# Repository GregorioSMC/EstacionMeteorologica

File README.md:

# Estacion Meteorologica
Diseño en software Eagle 
<hr>
<ul>
	<li> PCB Conexión ESP8266 (NodeMCU) y display 16X2 mediante protocolo i2C </li>
	<li> Conexion Sensor DHT11 </li>
	<li> 4 pines GPIO para Activacion Pre-Actuadores  </li>
</ul>

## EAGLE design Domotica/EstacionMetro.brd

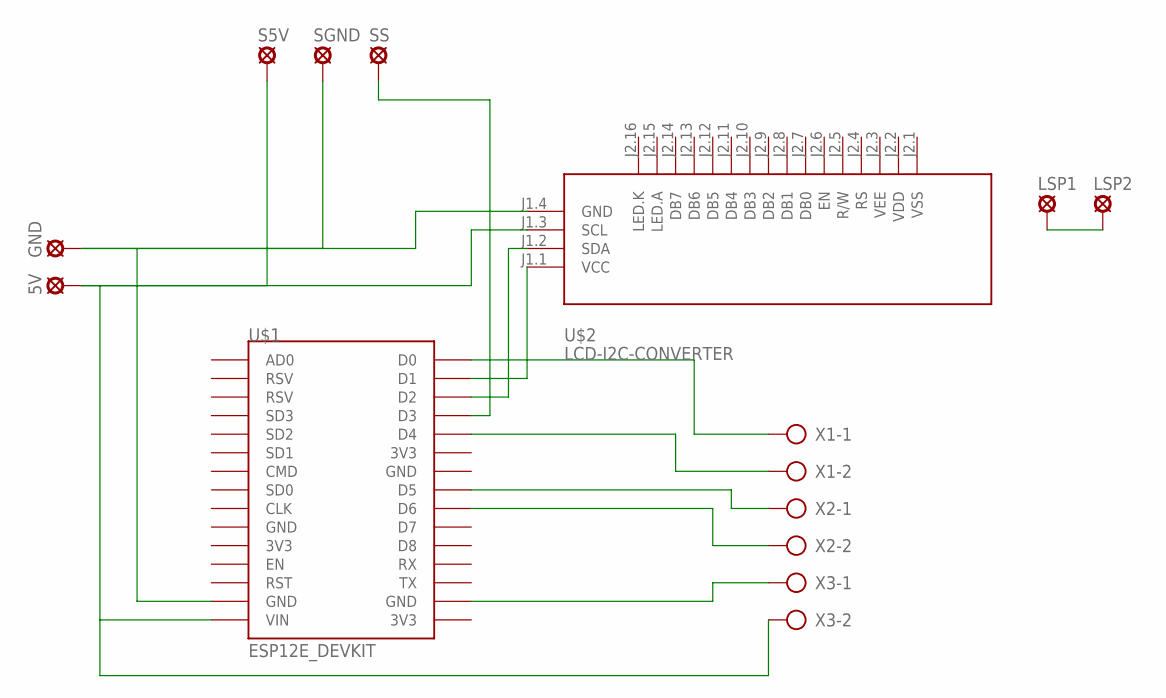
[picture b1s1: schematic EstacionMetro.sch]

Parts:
5V: SE11
GND: SE11
LSP1, LSP2: SE11
S5V: SE11
SGND: SE11
SS: SE11
U$1: ESP12E_DEVKIT
U$2: LCD-I2C-CONVERTER
X1, X2, X3: AK500/2

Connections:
unnamed: SS.MP, U$1.D3
unnamed: 5V.MP, S5V.MP, U$1.VIN, U$2.J1.3 (SCL), X3.2
unnamed: U$1.D1, U$2.J1.1 (VCC)
unnamed: U$1.D2, U$2.J1.2 (SDA)
unnamed: LSP1.MP, LSP2.MP
unnamed: GND.MP, SGND.MP, U$1.GND@1 (GND), U$2.J1.4 (GND)
unnamed: U$1.D0, X1.1
unnamed: U$1.D4, X1.2
unnamed: U$1.D5, X2.1
unnamed: U$1.D6, X2.2
unnamed: U$1.GND@3 (GND), X3.1

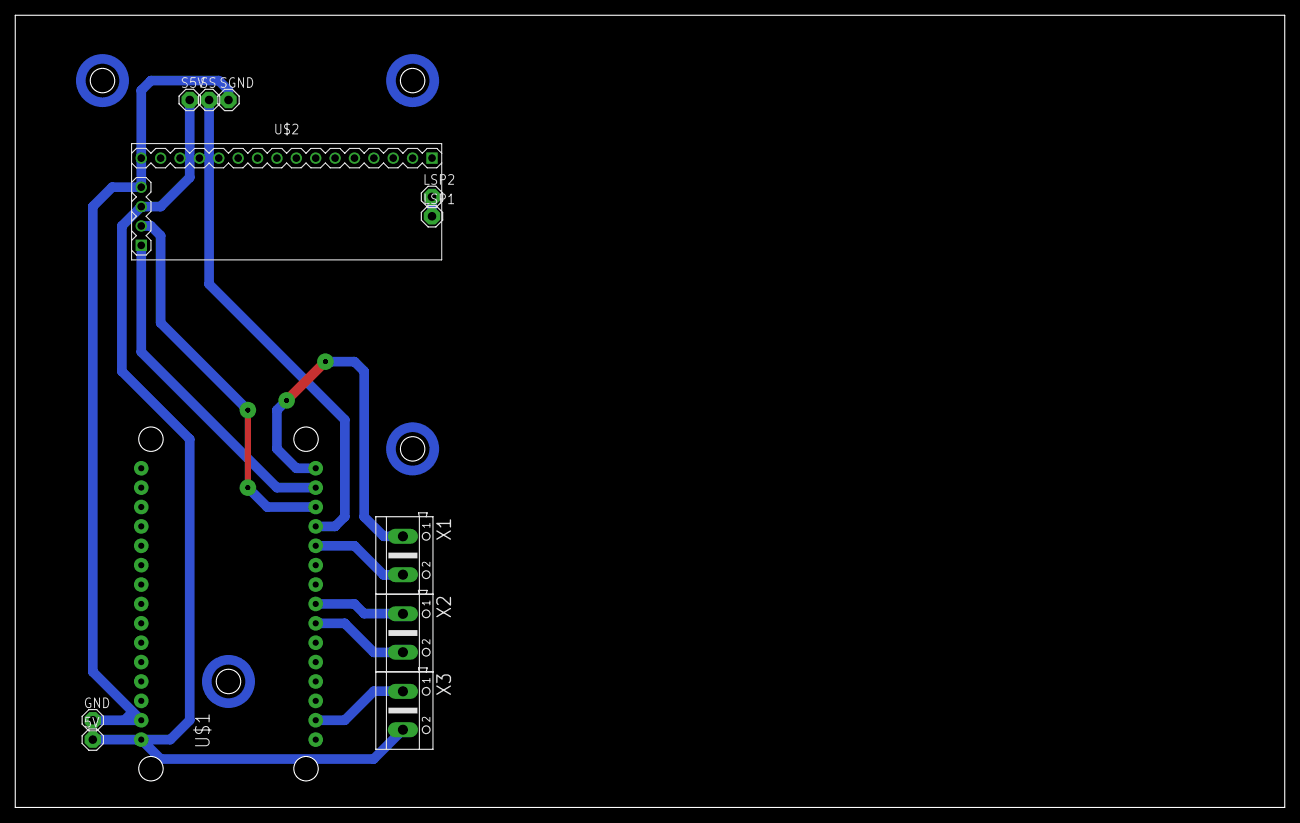
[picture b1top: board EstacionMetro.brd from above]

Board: 2 copper layers, 166.3 x 103.8 mm, 12 parts (0 on the bottom side), 11 nets.

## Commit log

2020-07-16 PCB_MCU_DISPLAY_DHT11
2020-07-16 Update README.md
    Descripción contenido

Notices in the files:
parts and their libraries:
diy-modules: Released under the Creative Commons Attribution 4.0 International License: http://creativecommons.org/licenses/by/4.0
